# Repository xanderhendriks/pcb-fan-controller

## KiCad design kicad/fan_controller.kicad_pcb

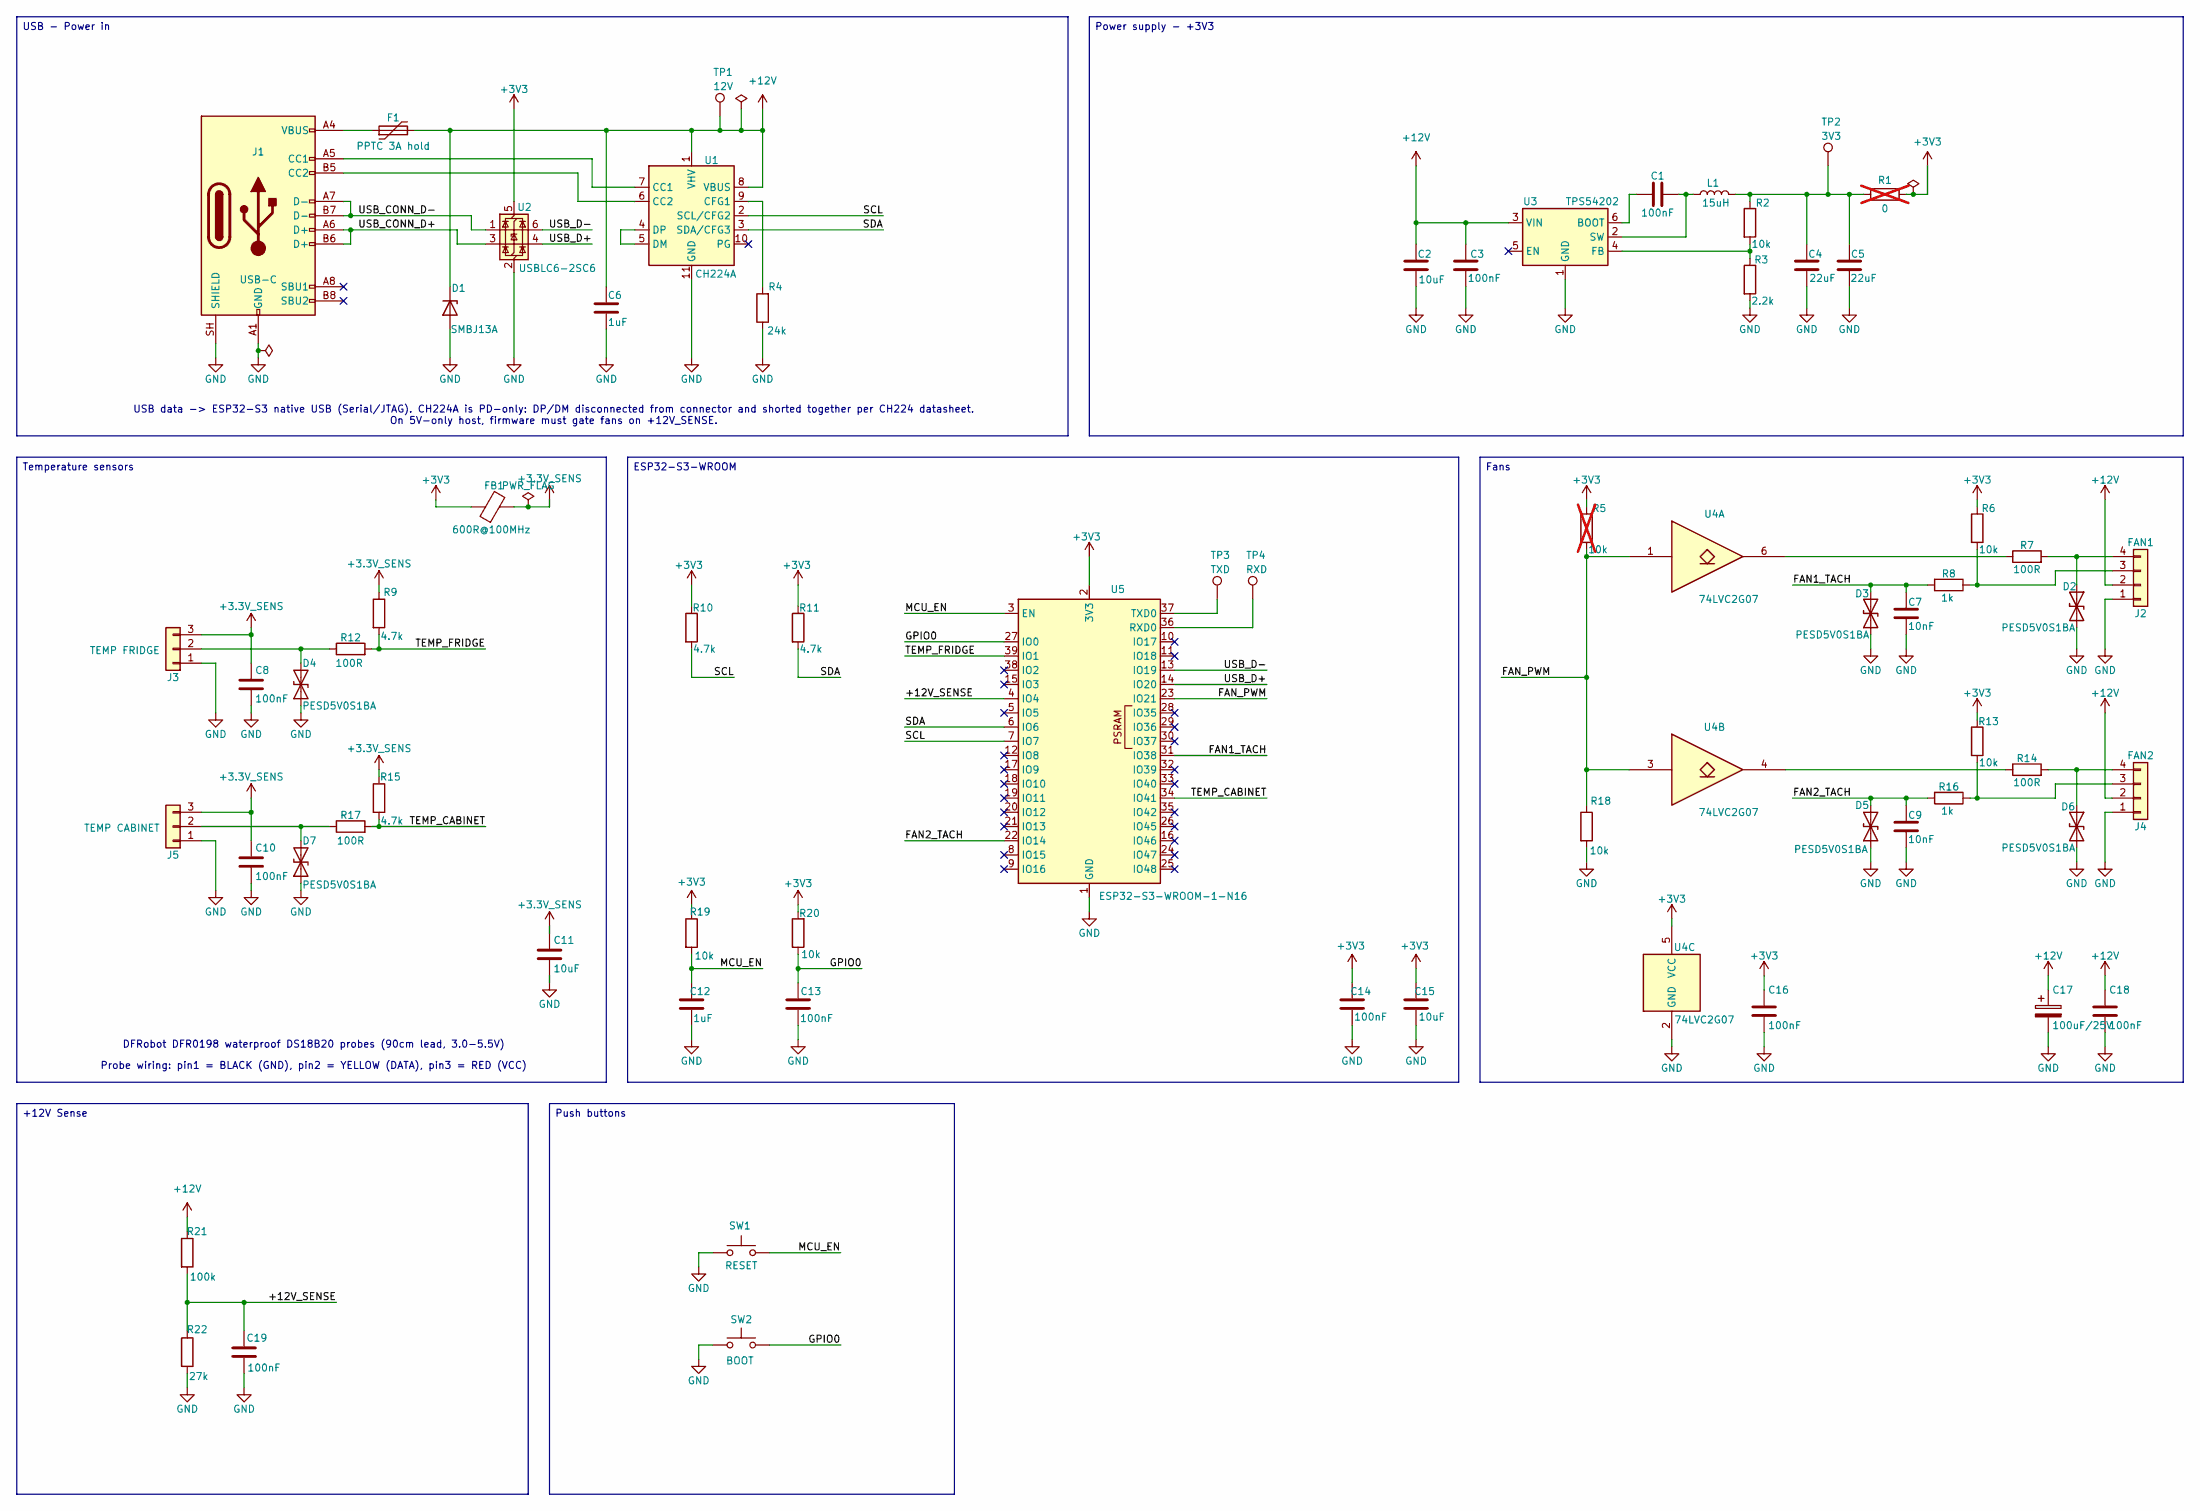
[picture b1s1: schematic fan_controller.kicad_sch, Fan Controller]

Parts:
C1, C3, C8, C10, C13, C14, C16, C18, C19: 100nF; C_0603_1608Metric; LCSC C14663
C2, C11, C15: 10uF; C_0805_2012Metric; LCSC C15850
C4, C5: 22uF; C_0805_2012Metric; LCSC C45783
C6, C12: 1uF; C_0603_1608Metric; LCSC C15849
C7, C9: 10nF; C_0603_1608Metric; LCSC C57112
C17: 100uF/25V; CP_Elec_6.3x7.7; LCSC C176675
D1: SMBJ13A; D_SMB; LCSC C151252
D2, D3, D4, D5, D6, D7: PESD5V0S1BA; D_SOD-323_HandSoldering; LCSC C19224
F1: PPTC 3A hold; 1812L300_24SLER; LCSC C1512049
FB1: 600R@100MHz; L_0603_1608Metric; LCSC C107335
J1: USB-C; USB_C_Receptacle_GCT_USB4105-xx-A_16P_TopMnt_Horizontal; LCSC C3020560
J2: FAN1; FanPinHeader_1x04_P2.54mm_Vertical; LCSC C240840
J3: TEMP FRIDGE; JST_XH_B3B-XH-A_1x03_P2.50mm_Vertical; LCSC C144394
J4: FAN2; FanPinHeader_1x04_P2.54mm_Vertical; LCSC C240840
J5: TEMP CABINET; JST_XH_B3B-XH-A_1x03_P2.50mm_Vertical; LCSC C144394
L1: 15uH; L_Bourns_SRN5040TA; LCSC C3222254
R1: 0; R_1206_3216Metric; LCSC C17888; not fitted
R2, R6, R13, R18, R19, R20: 10k; R_0603_1608Metric; LCSC C25804
R3: 2.2k; R_0603_1608Metric; LCSC C4190
R4: 24k; R_0603_1608Metric; LCSC C23352
R5: 10k; R_0603_1608Metric; LCSC C25804; not fitted
R7, R12, R14, R17: 100R; R_0603_1608Metric; LCSC C22775
R8, R16: 1k; R_0603_1608Metric; LCSC C21190
R9, R10, R11, R15: 4.7k; R_0603_1608Metric; LCSC C23162
R21: 100k; R_0603_1608Metric; LCSC C25803
R22: 27k; R_0603_1608Metric; LCSC C22967
SW1: RESET; SW_Push_1P1T_NO_CK_KMR2; LCSC C72443
SW2: BOOT; SW_Push_1P1T_NO_CK_KMR2; LCSC C72443
TP1: 12V; TestPoint_Pad_D1.0mm; LCSC N/A
TP2: 3V3; TestPoint_Pad_D1.0mm; LCSC N/A
TP3: TXD; TestPoint_Pad_D1.0mm; LCSC N/A
TP4: RXD; TestPoint_Pad_D1.0mm; LCSC N/A
U1: CH224A; SSOP-10-1EP_3.9x4.9mm_P1mm_EP2.1x3.3mm; LCSC C42459160
U2: USBLC6-2SC6; SOT-23-6; LCSC C7519
U3: TPS54202; SOT-23-6; LCSC C191884
U4: 74LVC2G07; SOT-23-6; LCSC C37708
U5: ESP32-S3-WROOM-1-N16; ESP32-S3-WROOM-1; LCSC C2913199

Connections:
+3.3V_SENS: C8.1, C10.1, C11.1, FB1.2, J3.3, J5.3, R9.1, R15.1
+3V3: C14.1, C15.1, C16.1, FB1.1, R1.2, R5.1, R6.1, R10.1, R11.1, R13.1, R19.1, R20.2, U2.5 (VBUS), U4.5 (VCC), U5.2 (3V3)
+12V: C2.1, C3.2, C6.1, C17.1, C18.1, D1.1 (K), F1.2, J2.2, J4.2, R21.1, TP1.1 (1_1), U1.1 (VHV), U1.8 (VBUS), U3.3 (VIN)
/+12V_SENSE: C19.1, R21.2, R22.1, U5.4 (IO4)
/FAN1_TACH: C7.1, D3.2 (A2), R8.2, U5.31 (IO38)
/FAN2_TACH: C9.1, D5.2 (A2), R16.2, U5.22 (IO14)
/FAN_PWM: R5.2, R18.1, U4.1, U4.3, U5.23 (IO21)
/GPIO0: C13.1, R20.1, SW2.2, U5.27 (IO0)
/MCU_EN: C12.1, R19.2, SW1.2, U5.3 (EN)
/SCL: R10.2, U1.2 (SCL/CFG2), U5.7 (IO7)
/SDA: R11.2, U1.3 (SDA/CFG3), U5.6 (IO6)
/TEMP_CABINET: R15.2, R17.2, U5.34 (IO41)
/TEMP_FRIDGE: R9.2, R12.2, U5.39 (IO1)
/USB_CONN_D+: J1.A6 (D+), J1.B6 (D+), U2.3 (I/O2)
/USB_CONN_D-: J1.A7 (D-), J1.B7 (D-), U2.1 (I/O1)
/USB_D+: U2.4 (I/O2), U5.14 (IO20)
/USB_D-: U2.6 (I/O1), U5.13 (IO19)
GND: C2.2, C3.1, C4.2, C5.2, C6.2, C7.2, C8.2, C9.2, C10.2, C11.2, C12.2, C13.2, C14.2, C15.2, C16.2, C17.2, C18.2, C19.2, D1.2 (A), D2.2 (A2), D3.1 (A1), D4.1 (A1), D5.1 (A1), D6.2 (A2), D7.1 (A1), J1.A1 (GND), J1.A12 (GND), J1.B1 (GND), J1.B12 (GND), J1.SH (SHIELD), J2.1, J3.1, J4.1, J5.1, R3.2, R4.1, R18.2, R22.2, SW1.1, SW2.1, U1.11 (GND), U2.2 (GND), U3.1 (GND), U4.2 (GND), U5.1 (GND), U5.40 (GND), U5.41 (GND)
unnamed: C4.1, C5.1, L1.2, R1.1, R2.1, TP2.1 (1_1)
unnamed: D2.1 (A1), J2.4, R7.2
unnamed: D4.2 (A2), J3.2, R12.1
unnamed: D6.1 (A1), J4.4, R14.2
unnamed: D7.2 (A2), J5.2, R17.1
unnamed: F1.1, J1.A4 (VBUS), J1.A9 (VBUS), J1.B4 (VBUS), J1.B9 (VBUS)
unnamed: J1.A5 (CC1), U1.7 (CC1)
unnamed: J1.B5 (CC2), U1.6 (CC2)
unnamed: J2.3, R6.2, R8.1
unnamed: J4.3, R13.2, R16.1
unnamed: R7.1, U4.6
unnamed: R14.1, U4.4
unnamed: R4.2, U1.9 (CFG1)
unnamed: U1.4 (DP), U1.5 (DM)
unnamed: C1.1, U3.6 (BOOT)
unnamed: R2.2, R3.1, U3.4 (FB)
unnamed: C1.2, L1.1, U3.2 (SW)
unnamed: TP4.1 (1_1), U5.36 (RXD0)
unnamed: TP3.1 (1_1), U5.37 (TXD0)

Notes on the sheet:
Probe wiring: pin1 = BLACK (GND), pin2 = YELLOW (DATA), pin3 = RED (VCC)
USB data -> ESP32-S3 native USB (Serial/JTAG). CH224A is PD-only: DP/DM disconnected from connector and shorted together per CH224 datasheet. On 5V-only host, firmware must gate fans on +12V_SENSE.
DFRobot DFR0198 waterproof DS18B20 probes (90cm lead, 3.0-5.5V)
Push buttons
Power supply - +3V3
ESP32-S3-WROOM
+12V Sense
Temperature sensors
Fans
USB - Power in

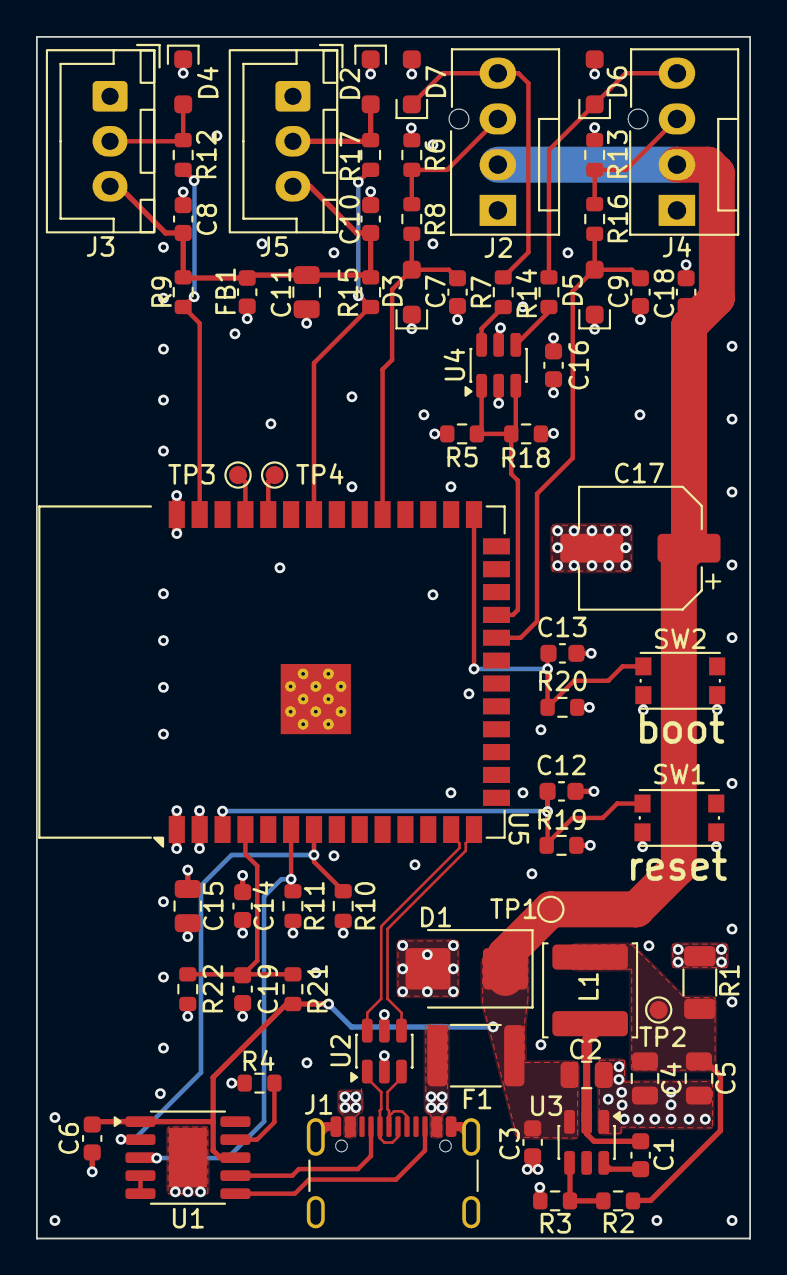
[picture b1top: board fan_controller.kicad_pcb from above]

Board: 4 copper layers, 39.6 x 66.8 mm, 67 parts (0 on the bottom side), 37 nets.
